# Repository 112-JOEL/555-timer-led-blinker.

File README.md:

# 555 Timer LED Blinker (NE55P)

This is a basic electronics project using the NE555 timer IC configured in **astable mode** to blink an LED. Designed for learning PCB design with KiCad, it demonstrates how to use common components like resistors, capacitors, and an LED.

## ⚙️ Features
- NE55P timer in astable mode
- Blinking LED output
- Easy through-hole components
- Designed in KiCad 7

## 🧰 Components Used
- NE555P (DIP-8)
- 1kΩ Resistor
- 10kΩ Resistor
- 10µF Capacitor (Electrolytic)
- 0.01µF Capacitor (Ceramic)
- Red LED
- Power Supply (5V–9V)
- 330Ω LED current-limiting resistor

## 🛠️ Files Included
- Schematic (`.kicad_sch`)
- PCB Layout (`.kicad_pcb`)
- 3D Preview
- Gerber Files (for manufacturing)
- PDF of schematic and PCB

## 🧪 Learning Goals
- Understand NE555 timer in astable mode
- Practice KiCad schematic and PCB design
- Learn component placement and routing

## 📚 References
- [555 Timer Basics – Electronics Tutorials](https://www.electronics-tutorials.ws/waveforms/555_timer.html)
- [KiCad Official Documentation](https://docs.kicad.org/)

---

**License:** [MIT](LICENSE)

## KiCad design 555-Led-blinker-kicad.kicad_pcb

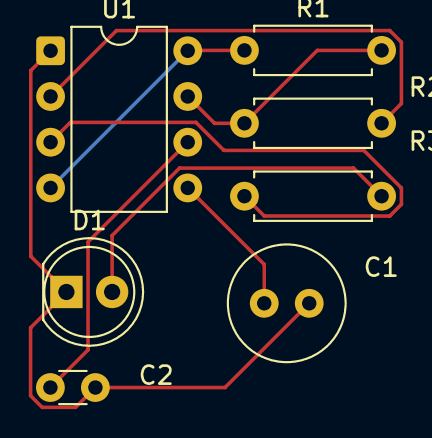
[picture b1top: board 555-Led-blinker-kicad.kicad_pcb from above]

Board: 2 copper layers, 7 parts (0 on the bottom side), 8 nets.

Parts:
C1: C; C_Radial_D6.3mm_H5.0mm_P2.50mm
C2: C_US; C_Disc_D3.0mm_W1.6mm_P2.50mm
D1: LED; LED_D5.0mm
R1, R2, R3: R; R_Axial_DIN0207_L6.3mm_D2.5mm_P7.62mm_Horizontal
U1: NE555P; DIP-8_W7.62mm

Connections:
+9V: R1.1, U1.4 (R), U1.8 (VCC)
GND: C1.2, C2.2, D1.1 (K), U1.1 (GND)
unnamed: D1.2 (A), R3.2
unnamed: C1.1, U1.5 (CV)
unnamed: R1.2, R2.1, U1.7 (DIS)
unnamed: R3.1, U1.3 (Q)
unnamed: C2.1, U1.6 (THR)
unnamed: R2.2, U1.2 (TR)

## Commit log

2025-06-13 Add NE555 timer LED blinker schematic and PCB layout
    - Created the schematic in KiCad with NE55P in astable mode
    - Designed a simple PCB layout with through-hole components
    - Added power input, LED, resistors, capacitors, and NE555
    - For learning basic PCB design and timer circuits
2025-06-13 README.md
